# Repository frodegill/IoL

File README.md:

# IoL
Internet Of Låve (english: Internet Of Barn, a play on the term Internet Of Things) is a system I've made for a colleague at Computas that also happens to have a farm.  
The systems consists of a Raspberry Pi server, a WiFi access point for local WiFi and a set of ESP8266 with custom shield reporting sensor values using MQTT over WiFi.  

The custom shield is used for these tasks:
* Outdoor temperature and humidity
* Indoor temperature and humidity
* Air duct temperature, humidity, air speed and air pressure
* Two temperature and humidity sensors to put into the grain

The goal of this project is to calculate when outside air blown indoors is drier than the air that is already indoor, and thus starting a fan running on cheap electricity would be enough to dry the grain instead of having the air dryer running on expensive diesel.

### pictures

Here is a picture of the barn full of grain. The air duct comes down from the ceiling and under the left side window. There are air vents crossing the room running from the left side air duct.  

All sensor values are sent by MQTT to Mosquitto running on the Raspberry Pi. A local installation of Node-Red captures the values, massages them, and stores them in InfluxDB. A Grafana dashboard fetches data from InfluxDB and makes informative graphs. In the screenshot below you can see the period where the fan was manually turned on (thus creating wind speed and pressure difference in the air duct). This was immediately after the grain was harvested, so the results are admittedly better than usual, but you can see that the temperature and humidity in the grain will trend towards that in the air duct. As the outside humidity adjusted for indoor temperature is higher than the indoor humidity at the time of the screenshot, running the fan does not result in dryer grain and was only done for demonstration purposes.  

The barn does not have an internet connection, but the WiFi access point exposes Grafana running on the Raspberry Pi, and accessing it from a phone connected to the same WiFi network works like a charm.

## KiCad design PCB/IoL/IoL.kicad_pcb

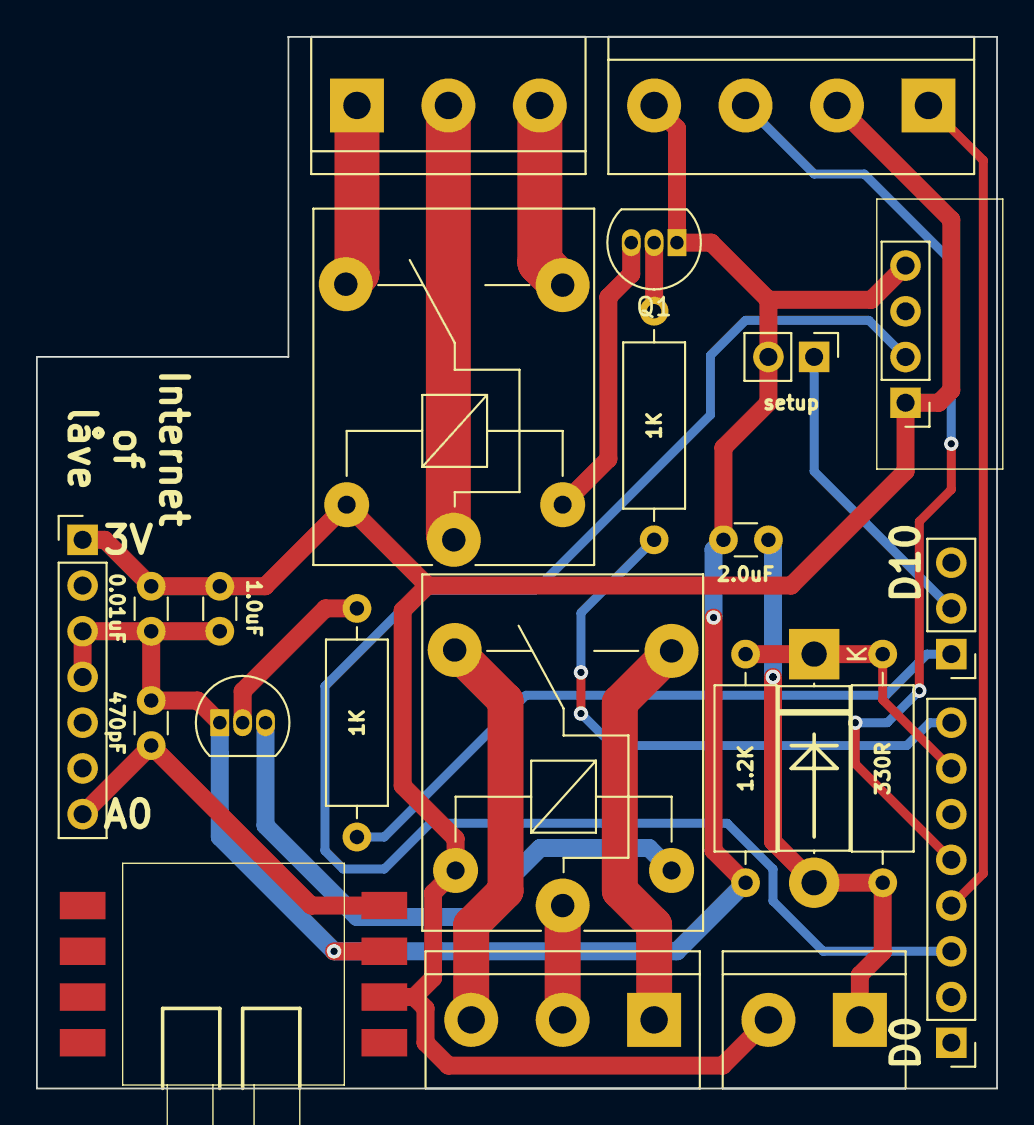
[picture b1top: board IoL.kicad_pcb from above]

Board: 2 copper layers, 53.3 x 58.4 mm, 23 parts (0 on the bottom side), 21 nets.

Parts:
C1: 470pF; C_Disc_D3.0mm_W1.6mm_P2.50mm
C2: 1.0uF; C_Disc_D3.0mm_W1.6mm_P2.50mm
C3: 0.01uF; C_Disc_D3.0mm_W1.6mm_P2.50mm
C4: 2.0uF; C_Disc_D3.0mm_W1.6mm_P2.50mm
D1: D; D_5W_P12.70mm_Horizontal
J1, J9: Conn_01x03_Male; TerminalBlock_bornier-3_P5.08mm
J2: Conn_01x07_Male; PinHeader_1x07_P2.54mm_Vertical
J3: Conn_01x04_Male; TerminalBlock_bornier-4_P5.08mm
J5: Conn_01x02_Male; TerminalBlock_bornier-2_P5.08mm
J6: Conn_01x02_Male; PinHeader_1x02_P2.54mm_Vertical
J7: Conn_01x03_Male; PinHeader_1x03_P2.54mm_Vertical
J8: Conn_01x08_Male; PinHeader_1x08_P2.54mm_Vertical
K1, K2: SANYOU_SRD_Form_C; Relay_SPDT_SANYOU_SRD_Series_Form_C
Q1, Q2: BC337; TO-92_Inline
R1: 1.2K; R_Axial_DIN0309_L9.0mm_D3.2mm_P12.70mm_Horizontal
R2: 330R; R_Axial_DIN0309_L9.0mm_D3.2mm_P12.70mm_Horizontal
R3, R4: 1K; R_Axial_DIN0309_L9.0mm_D3.2mm_P12.70mm_Horizontal
U1: MP3V5004G
U2: AM2302

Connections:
+3V3: C2.1, C3.1, J2.1, J3.2, J5.2, K1.5, K2.5, U1.2, U2.1
GND: C1.2, C2.2, C3.2, C4.2, J2.3, J2.4, J3.4, J6.2, Q1.1, Q2.1, R1.2, U1.3, U2.4
unnamed: C1.1, J2.7, U1.4
unnamed: C4.1, D1.2, J5.1, R2.2
unnamed: D1.1, J8.7, R1.1, R2.1
unnamed: J1.1, K1.4
unnamed: J1.2, K1.1
unnamed: J1.3, K1.3
unnamed: J3.1, J8.4
unnamed: J3.3, J8.5
unnamed: J6.1, J7.2
unnamed: J7.1, R3.1
unnamed: J8.3, U2.2
unnamed: J8.8, R4.1
unnamed: J9.1, K2.3
unnamed: J9.2, K2.1
unnamed: J9.3, K2.4
unnamed: K1.2, Q1.3
unnamed: K2.2, Q2.3
unnamed: Q1.2, R4.2
unnamed: Q2.2, R3.2

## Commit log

2017-12-31 Networking
2018-06-14 Replaced with empty sensor framework
2018-06-28 Actual functionality..
2018-06-29 Windspeed sensor
2018-07-02 Use A and B instead of 1 and 2 for temp sensors
2018-07-02 Munin config values
2018-08-14 Use only one I2C SHT precision temp sensor. And MQTT WIP
2018-08-14 Removed unused code
2019-07-28 Lots of small fixes :-/
2019-07-28 Added KiCAD files
2019-07-31 More pin renaming
2019-07-31 Use bool
2019-07-31 Minor tweaks
2019-08-01 Dont retry indefinitly when connecting to MQTT
2019-08-01 Let MQTT handle fan and heater
2019-08-01 Fixed whitespace
2019-08-18 Added Node-RED flow
2023-09-28 Added some photos
